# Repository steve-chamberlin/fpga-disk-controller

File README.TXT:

Compiled by Steve Chamberlin
steve@bigmessowires.com
January 28, 2019

//\\//\\//\\//\\//\\//\\//\\//\\//\\//\\//\\//\\//\\//\\//\\//\\//\\//\\//\\//\\

I'm sharing the FPGA disk controller design because I don't currently have the time or resources to pursue its further development on my own, but want the Apple II collector community to get the benefit of the progress I've made to date. 

See LICENSE.TXT for details on the license terms for this design.

The marks "Yellowstone", "BMOW", and "Big Mess o' Wires" are not covered by this license, and are reserved for my exclusive use. You are not permitted to use any of these words in the name of any clone or derivative products based on this design. You will need to choose a new name for your clone or derivative product.

//\\//\\//\\//\\//\\//\\//\\//\\//\\//\\//\\//\\//\\//\\//\\//\\//\\//\\//\\//\\

GROUND RULES
------------

Please don't send me detailed questions and requests for help with this design, or expect me to be your engineering consultant. I'm releasing the design to the community because I don't have time to pursue it myself. That means I can't work on it for you, either. The design is released as-is, with no promise of technical support. I may be able to answer general questions, but the rest is up to you.  

WHAT IS THIS?
-------------

Yellowstone is the code name for an Apple II disk controller card that's based on an FPGA, rather than using discrete logic chips and ROM chips. By reprogramming the FPGA, the card can be made to emulate various other disk controller cards made by Apple in the 1980s and 1990s. The work so far has focused on emulating an Apple Liron disk controller card, but it would also be easy to emulate a Disk II controller card. It's theoretically also possible to emulate a Disk 3.5 controller card, though this possibility has not been explored in detail.

WHAT'S LIRON?
-------------

The Liron disk controller was introduced by Apple in 1985. More formally known as the Apple II UniDisk 3.5 Controller, it's designed to work with a new generation of "smart" disk drives more sophisticated than the venerable Disk II 5.25 inch floppy drive. The smart disk port on the Liron is appropriately named the Smartport, and it can communicate with block-based storage devices such as the Unidisk 3.5 (an early 800K drive) and Smartport-based Apple II hard drives.

Why care about the Liron? The Apple IIc and Apple IIgs have integrated disk ports with built-in Smartport functionality, but for the earlier Apple II+ and IIe, the Liron is the only way to get a Smartport. For owners of the BMOW Floppy Emu disk emulator, having a Liron card makes it possible to use the Floppy Emu as an external hard drive for the II+ and IIe. Unfortunately finding a Liron is difficult, and although they occasionally turn up on eBay, they’re quite expensive. That makes cloning the Liron a desirable goal.

HOW IT WORKS
------------

The FPGA disk controller card is little more than an FPGA, a voltage regulator, and a set of level-shifting bus transceivers. The FPGA replaces all of the 7400-series discrete logic chips typically found on a disk controller card. Verilog (hardware description language) replacements for all of the 7400-series parts and other logic were written and programmed into the FPGA. This also includes a full Verilog implmentation of the Apple IWM chip. 

The FPGA also replaces the ROM chip containing the boot code for the card. The Apple II executes this code during power-up, and the code knows how to find and load sector 0 from the attached disk drive. The code was obtained from a ROM dump from a real Liron card.

The prototype card also includes a footprint for an 8-pin SPI flash memory chip. It is not used by the current FPGA code, and the chip can be omitted. The idea was that a small number of disk images could be stored in SPI flash memory, so the card could function both as a disk controller and as a disk emulator, but this was never implemented.

The card has a standard 10 x 2 pin disk connector on board. It can be connected directly to a BMOW Floppy Emu disk emulator, using a standard ribbon cable. But for a full Liron clone and connecton to a Unidisk 3.5, a DB-19 female connector is required. A design for a DB-19F adapter PCB is included here, and the adapter can be connected to the disk controller card with a short ribbon cable. The DB-19F is still available from surplus electronics suppliers in small quantities.

PROJECT STATUS
--------------

See https://www.bigmessowires.com/category/yellowstone/ for a complete history of work involving the FPGA disk controller.

The FPGA disk controller card was designed by Steve Chamberlin at Big Mess o' Wires during the summer of 2017, but the first prototype card wasn't built and tested until January 2018. The version 1.0 card had errors with the wiring for the output enable signal on one of the bus transceiver chips, and it required a few hand-soldered path wires to fix. After further development, the prototype card was demonstrated to work as a Liron clone, in both an Apple IIe enhanced computer and an Apple IIgs. It worked for controlling a real Unidisk 3.5 drive, as well as a BMOW Floppy Emu disk emulator configured for Smartport emulation mode.

Later testing discovered that the FPGA disk controller card worked reliably when it was the only card installed, but other cards were also present, it sometimes malfunctioned. The more other cards present, the worse the rate of errors became. This was diagnosed as a likely termination or contention problem on the Apple II data bus, and various fixes were tried unsuccessfully. After March 2018, I lost interest in researching the problem further, and no more work has occurred since then.

The design provided here is version 1.1, and it fixes the output enable problem from version 1.0.

WHERE TO START
--------------

Open the FPGA disk controller design (Liron clone) in EAGLE. Export Gerber files and send them to your favorite PCB fabricator. If desired, do the same for the DB19F adapter design.

Purchase the chips and other parts listed in the BOM. 

Assemble the card. I did it by hand, you can do it too. A syringe of solder paste and a hot plate or toaster oven works nicely.

Get a Lattice JTAG programmer or appropriate clone. Some clones don't handle 3.3V logic correctly. Maybe spend the extra money for a genuine Lattice programmer.

Install the Lattice Diamond software.

Apply 5V power to the card at jumper J4. Do not insert the card into your Apple II yet.

Program the FPGA with the bitstream for the Liron clone design - liron_fpgatop.jed

Insert the card in your Apple II. Remove any other cards that are present.

Connect a Smartport-compatible disk drive, such as a BMOW Floppy Emu disk emulator that's configured for Smartport emulation mode, or an Apple Unidisk 3.5 drive.

Turn on the Apple II. It should boot from the attached drive.

NEXT STEPS
----------

The bus termination or bus contention problem must be solved, in order to get a robust card that works smoothly when other cards are also present. See the blog posts from February-March 2018 for more details about what was already tried. A solution will require a person who's experienced at electronic design, and has appropriate test equipment such as an oscilloscope and logic analyzer.

The current design uses a Lattice MachXO2 1200HC FPGA, and a Lattice JTAG programmer (or compatible) is required for programming it. The XO2-1200HC has more logic resources than are actually necessary for the Liron clone design. The cheaper XO2-640 or XO2-256 could be substituted instead. They are mostly or entirely pin-compatible with the XO2-1200HC.

Programming the FPGA with a JTAG programmer is fine for development use, but end users are unlikely to have one. If reprogramming by the end user is desired (say to switch between Liron and Disk 3.5 emulation behaviors), a different method of FPGA programming will need to be developed.

FILES
-----

eagle/ - directory containing EAGLE designs for the FPGA disk controller card, the DB19F adapter, and a reverse-engineered schematic of the original Liron card.
eagle/FPGA disk controller/bom.xslx - bill of materials needed to assemble the card.
lattice/ - directory containing the Verilog and other code for the Liron clone design for the card.
yellowstone_blink/ - directory containing the Verilog and other code for a simple LED blink example. This can be used to verify that the FPGA is working.
yellowstone_blink_tcr.dir/ - directory containing some junk generated by the Lattice Diamond software.
disasm.asm, liron.asm - two different disassemblies of the original Liron card's boot ROM
LIRONALL.BIN - binary file with the original Liron card's boot ROM
rom-full-4k.mem - the Liron boot ROM in a format compatible with the Lattice Diamond software.
README.TXT - this file
LICENSE.TXT - details about the license for the design

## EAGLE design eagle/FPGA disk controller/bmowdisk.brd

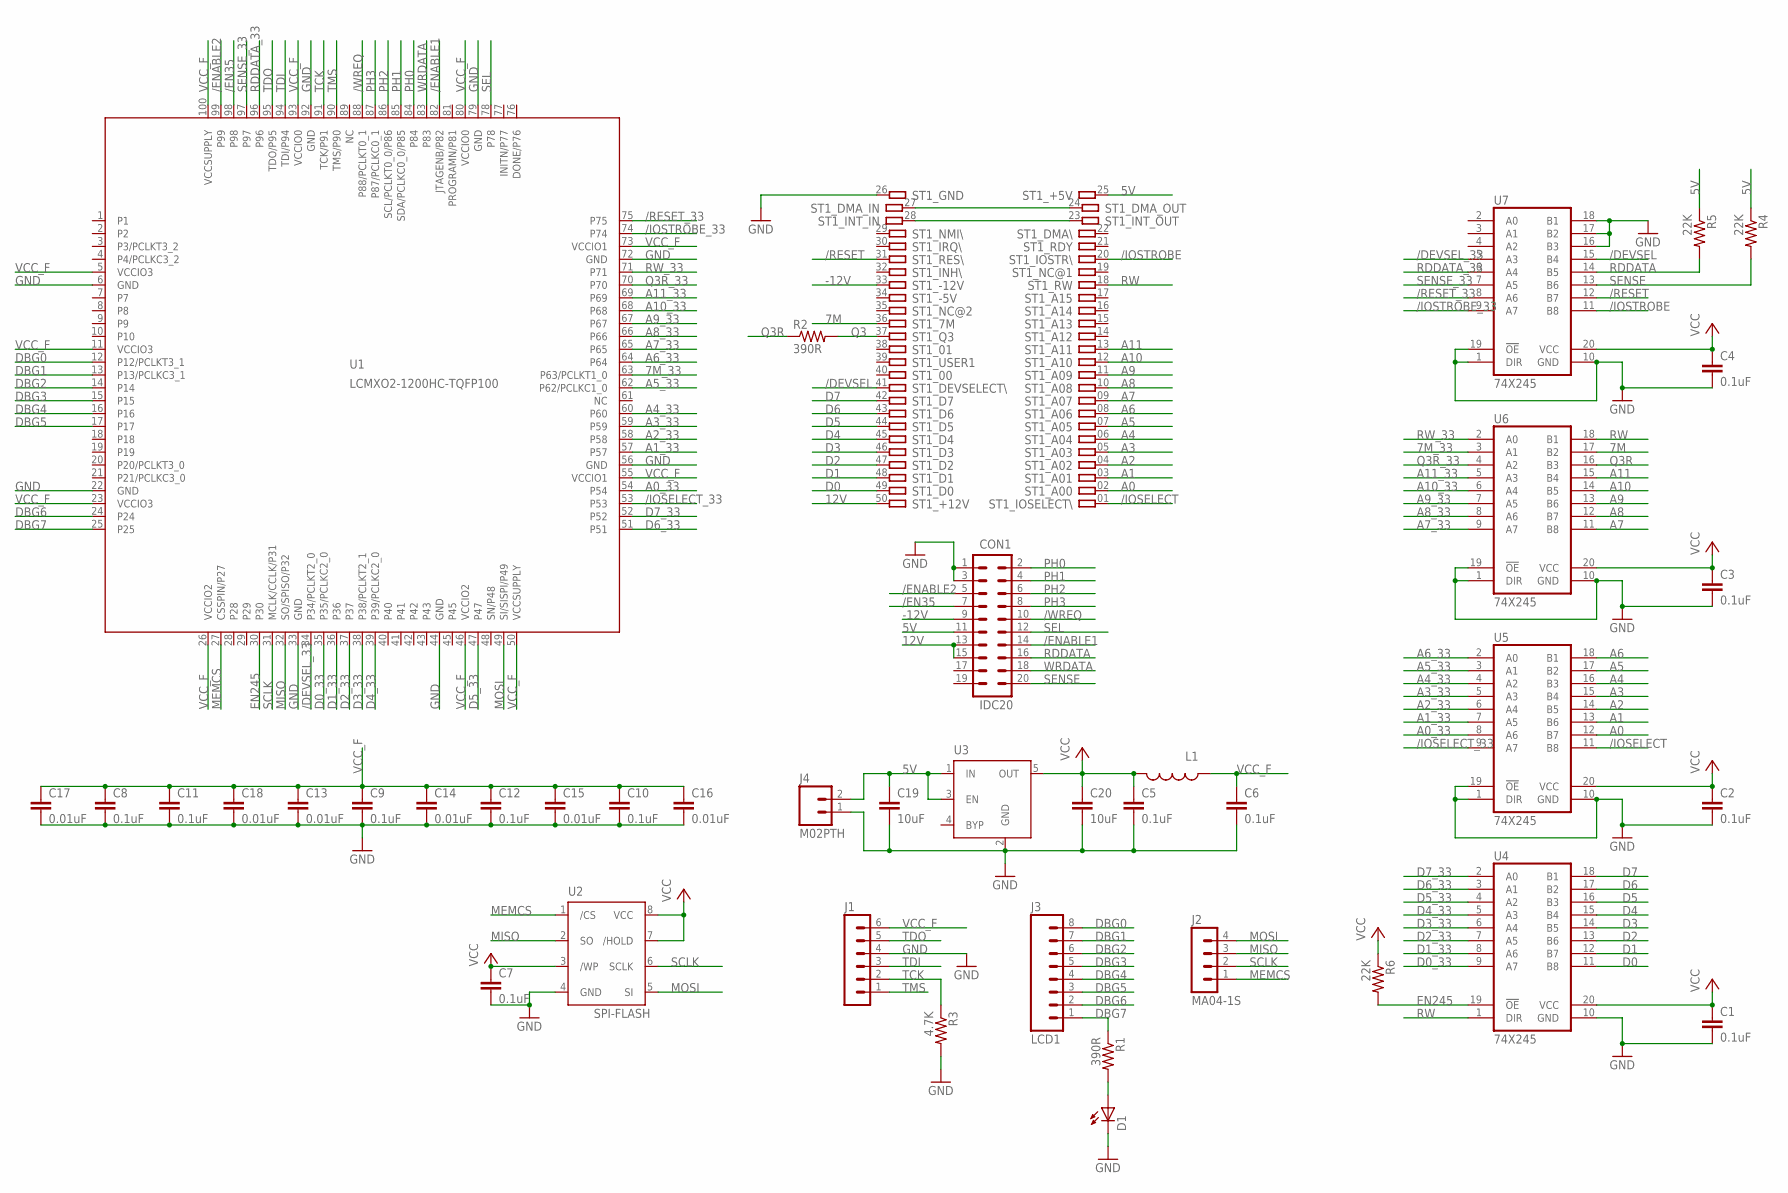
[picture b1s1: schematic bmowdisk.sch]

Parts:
C1, C2, C3, C4, C5, C6, C7, C8, C9, C10, C11, C12: 0.1uF; 0805
C13, C14, C15, C16, C17, C18: 0.01uF; 0805
C19, C20: 10uF; 0805
CON1: IDC20
D1: LEDCHIP-LED0805; CHIP-LED0805
J1: MA06-1NORMAL; MA06-1
J2: MA04-1S; MA04-1
J3: LCD1; 1X08
J4: M02PTH; 1X02
L1: INDUCTOR0805; 0805
R1, R2: 390R; 0805
R3: 4.7K; 0805
R4, R5, R6: 22K; 0805
ST1: A2-50PINMINI; A2-50PIN-MINI
U1: LCMXO2-1200HC-TQFP100; TQFP100
U2: SPI-FLASH; SOIC08
U3: MIC5219XX; SOT23-5
U4, U5, U6, U7: 74X245; SSOP20

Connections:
5V: C19.1, CON1.11, J4.2, R4.1, R5.1, ST1.25, U3.1 (IN), U3.3 (EN)
7M: ST1.36, U6.17 (B2)
7M_33: U1.63 (P63/PCLKT1_0), U6.3 (A1)
12V: CON1.13, CON1.15, ST1.50
-12V: CON1.9, ST1.33
/DEVSEL: ST1.41, U7.15 (B4)
/DEVSEL_33: U1.34 (P34/PCLKT2_0), U7.5 (A3)
/EN35: CON1.7, U1.98
/ENABLE1: CON1.14, U1.82 (JTAGENB/P82)
/ENABLE2: CON1.5, U1.99
/IOSELECT: ST1.01, U5.11 (B8)
/IOSELECT_33: U1.53, U5.9 (A7)
/IOSTROBE: ST1.20, U7.11 (B8)
/IOSTROBE_33: U1.74, U7.9 (A7)
/RESET: ST1.31, U7.12 (B7)
/RESET_33: U1.75, U7.8 (A6)
/WREQ: CON1.10, U1.88 (P88/PCLKT0_1)
A0: ST1.02, U5.12 (B7)
A0_33: U1.54, U5.8 (A6)
A1: ST1.03, U5.13 (B6)
A1_33: U1.57, U5.7 (A5)
A2: ST1.04, U5.14 (B5)
A2_33: U1.58, U5.6 (A4)
A3: ST1.05, U5.15 (B4)
A3_33: U1.59, U5.5 (A3)
A4: ST1.06, U5.16 (B3)
A4_33: U1.60, U5.4 (A2)
A5: ST1.07, U5.17 (B2)
A5_33: U1.62 (P62/PCLKC1_0), U5.3 (A1)
A6: ST1.08, U5.18 (B1)
A6_33: U1.64, U5.2 (A0)
A7: ST1.09, U6.11 (B8)
A7_33: U1.65, U6.9 (A7)
A8: ST1.10, U6.12 (B7)
A8_33: U1.66, U6.8 (A6)
A9: ST1.11, U6.13 (B6)
A9_33: U1.67, U6.7 (A5)
A10: ST1.12, U6.14 (B5)
A10_33: U1.68, U6.6 (A4)
A11: ST1.13, U6.15 (B4)
A11_33: U1.69, U6.5 (A3)
D0: ST1.49, U4.11 (B8)
D0_33: U1.35 (P35/PCLKC2_0), U4.9 (A7)
D1: ST1.48, U4.12 (B7)
D1_33: U1.36, U4.8 (A6)
D2: ST1.47, U4.13 (B6)
D2_33: U1.37, U4.7 (A5)
D3: ST1.46, U4.14 (B5)
D3_33: U1.38 (P38/PCLKT2_1), U4.6 (A4)
D4: ST1.45, U4.15 (B4)
D4_33: U1.39 (P39/PCLKC2_0), U4.5 (A3)
D5: ST1.44, U4.16 (B3)
D5_33: U1.47, U4.4 (A2)
D6: ST1.43, U4.17 (B2)
D6_33: U1.51, U4.3 (A1)
D7: ST1.42, U4.18 (B1)
D7_33: U1.52, U4.2 (A0)
DBG0: J3.8, U1.12 (P12/PCLKT3_1)
DBG1: J3.7, U1.13 (P13/PCLKC3_1)
DBG2: J3.6, U1.14
DBG3: J3.5, U1.15
DBG4: J3.4, U1.16
DBG5: J3.3, U1.17
DBG6: J3.2, U1.24
DBG7: J3.1, R1.1, U1.25
EN245: R6.2, U1.30, U4.19 (!OE)
GND: C1.2, C2.2, C3.2, C4.2, C5.2, C6.2, C7.2, C8.2, C9.2, C10.2, C11.2, C12.2, C13.2, C14.2, C15.2, C16.2, C17.2, C18.2, C19.2, C20.2, CON1.1, CON1.3, D1.C, J1.4, J4.1, R3.2, ST1.26, U1.6 (GND), U1.22 (GND), U1.33 (GND), U1.44 (GND), U1.56 (GND), U1.72 (GND), U1.79 (GND), U1.92 (GND), U2.4 (GND), U3.2 (GND), U4.10 (GND), U5.1 (DIR), U5.10 (GND), U5.19 (!OE), U6.1 (DIR), U6.10 (GND), U6.19 (!OE), U7.1 (DIR), U7.10 (GND), U7.16 (B3), U7.17 (B2), U7.18 (B1), U7.19 (!OE)
MEMCS: J2.1, U1.27 (CSSPIN/P27), U2.1 (/CS)
MISO: J2.3, U1.32 (SO/SPISO/P32), U2.2 (SO)
MOSI: J2.4, U1.49 (SI/SISPI/P49), U2.5 (SI)
unnamed: ST1.24, ST1.27
unnamed: ST1.23, ST1.28
unnamed: D1.A, R1.2
PH0: CON1.2, U1.84
PH1: CON1.4, U1.85 (SDA/PCLKC0_0/P85)
PH2: CON1.6, U1.86 (SCL/PCLKT0_0/P86)
PH3: CON1.8, U1.87 (P87/PCLKC0_1)
Q3: R2.2, ST1.37
Q3R: R2.1, U6.16 (B3)
Q3R_33: U1.70, U6.4 (A2)
RDDATA: CON1.16, R5.2, U7.14 (B5)
RDDATA_33: U1.96, U7.6 (A4)
RW: ST1.18, U4.1 (DIR), U6.18 (B1)
RW_33: U1.71, U6.2 (A0)
SCLK: J2.2, U1.31 (MCLK/CCLK/P31), U2.6 (SCLK)
SEL: CON1.12, U1.78
SENSE: CON1.20, R4.2, U7.13 (B6)
SENSE_33: U1.97, U7.7 (A5)
TCK: J1.2, R3.1, U1.91 (TCK/P91)
TDI: J1.3, U1.94 (TDI/P94)
TDO: J1.5, U1.95 (TDO/P95)
TMS: J1.1, U1.90 (TMS/P90)
VCC: C1.1, C2.1, C3.1, C4.1, C5.1, C7.1, C20.1, L1.2, R6.1, U2.3 (/WP), U2.7 (/HOLD), U2.8 (VCC), U3.5 (OUT), U4.20 (VCC), U5.20 (VCC), U6.20 (VCC), U7.20 (VCC)
VCC_F: C6.1, C8.1, C9.1, C10.1, C11.1, C12.1, C13.1, C14.1, C15.1, C16.1, C17.1, C18.1, J1.6, L1.1, U1.5 (VCCIO3), U1.11 (VCCIO3), U1.23 (VCCIO3), U1.26 (VCCIO2), U1.46 (VCCIO2), U1.50 (VCCSUPPLY), U1.55 (VCCIO1), U1.73 (VCCIO1), U1.80 (VCCIO0), U1.93 (VCCIO0), U1.100 (VCCSUPPLY)
WRDATA: CON1.18, U1.83

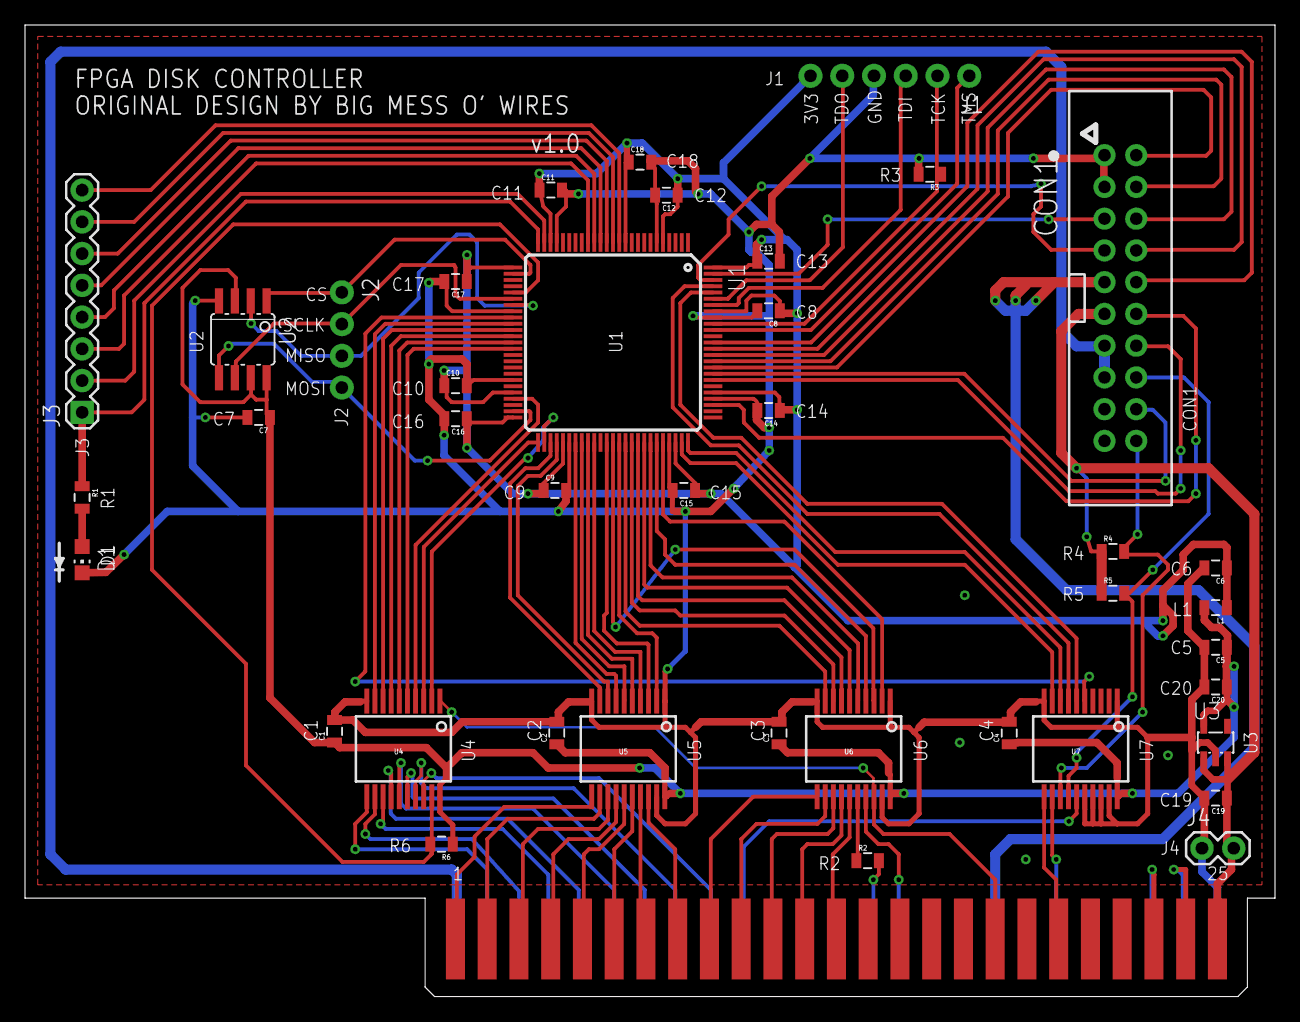
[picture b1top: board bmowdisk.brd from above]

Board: 2 copper layers, 100.0 x 77.7 mm, 41 parts (0 on the bottom side), 95 nets.

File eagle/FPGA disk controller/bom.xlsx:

Designation | Description | Manufacturer Part Number | Acceptable Substitutes | Source 1 | Source 2 | notes
U1 | MachXO2 1200HC FPGA, 100-pin TQFP package | Lattice LCMXO2-1200HC-4TG100C | none | https://www.digikey.com/product-detail/en/lattice-semiconduc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 |  | Could downsize to XO2-640 or XO2-256 if extra ROM space isn't needed. Confirm p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
U2 | SPI Flash memory, 8-pin SIOC package | Adesto AT25SF161-SSHD-T | similar | https://www.digikey.com/product-detail/en/adesto-technologie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 |  | Optional. Use for disk image storage, or ROM code if it's fast enough.
U3 | 300mA 3.3V LDO regulator, 5V input, SOT235 package | Micrel MIC5504-3.3YM5-TR | similar | https://www.digikey.com/product-detail/en/microchip-technolo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 | https://www.arrow.com/en/products/mic5504-3.3ym5-tr/microchi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
U4,U5,U6,U7 | 8-bit bus transceiver 74LVC245 | Nexperia 74LVC245ADB,118 | similar | https://www.digikey.com/product-detail/en/nexperia-usa-inc/7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,118/1727…
CON1 | IDC-20 male shrouded header | On Shore Technology 302-S201 | generic | http://www.digikey.com/product-detail/en/302-S201/ED10524-ND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 | http://www.digikey.com/product-detail/en/SBH11-PBPC-D10-ST-B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
J1 | 6x1 pin 0.1 inch male header, PTH | MC34743 | generic | http://www.newark.com/multicomp/mc34743/board-board-connecto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 | https://www.digikey.com/product-detail/en/sullins-connector-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 | Optional, JTAG port.
J2 | 4x1 pin 0.1 inch male header, PTH | MC34743 | generic | http://www.newark.com/multicomp/mc34743/board-board-connecto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 | https://www.digikey.com/product-detail/en/sullins-connector-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 | Optional, SPI port.
J3 | 8x1 pin 0.1 inch male header, PTH | MC34743 | generic | http://www.newark.com/multicomp/mc34743/board-board-connecto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 | https://www.digikey.com/product-detail/en/sullins-connector-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 | Optional, debug port.
J4 | 2x1 pin 0.1 inch male header, PTH | MC34743 | generic | http://www.newark.com/multicomp/mc34743/board-board-connecto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 | https://www.digikey.com/product-detail/en/sullins-connector-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 | Optional, 5V supply connector
D1 | LED, green, 0805 package, about 12 mcd | KP-2012SGC | generic | http://www.newark.com/kingbright/kp-2012sgc/led-green-1-25mm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 | https://www.digikey.com/product-detail/en/osram-opto-semicon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 | debug LED
L1 | ferrite bead 0805 | BKP2125HS600-T | generic | https://www.digikey.com/product-detail/en/taiyo-yuden/BKP212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
R1,R2 | 390 ohm resistor, 0805 package, 1/8W, 20% | RMCF0805JT390R | generic | https://www.digikey.com/product-detail/en/stackpole-electron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
R3 | 4.7K ohm resistor, 0805 package, 1/8W, 20% | RMCF0805JT4K70 | generic | https://www.digikey.com/product-detail/en/stackpole-electron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
R4,R5,R6 | 22K ohm resistor, 0805 package, 1/8W, 20% | RMCF0805JT22K0 | generic | https://www.digikey.com/product-detail/en/stackpole-electron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
C1-C12 | 0.1uF ceramic capacitor, 0805 package, 50V, 20% | CL21B104MBCNNNC | generic | https://www.digikey.com/product-detail/en/samsung-electro-me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
C13-C18 | 0.01uF ceramic capacitor, 0805 package, 50V, 20% | CL21B103KBANNNC | generic | https://www.digikey.com/product-detail/en/samsung-electro-me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
C19,C20 | 10uF ceramic capacitor, 0805 package, 6.3V, 20% | CL21A106KQCLRNC | generic | http://www.newark.com/avx/08056d106kat2a/ceramic-capacitor-1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 | https://www.digikey.com/product-detail/en/samsung-electro-me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
MISC1 | DB19-F |  |  |  |  | not required for Floppy Emu, but required for real drives
MISC2 | DB19-F adapter board |  |  |  |  | not required for Floppy Emu, but required for real drives

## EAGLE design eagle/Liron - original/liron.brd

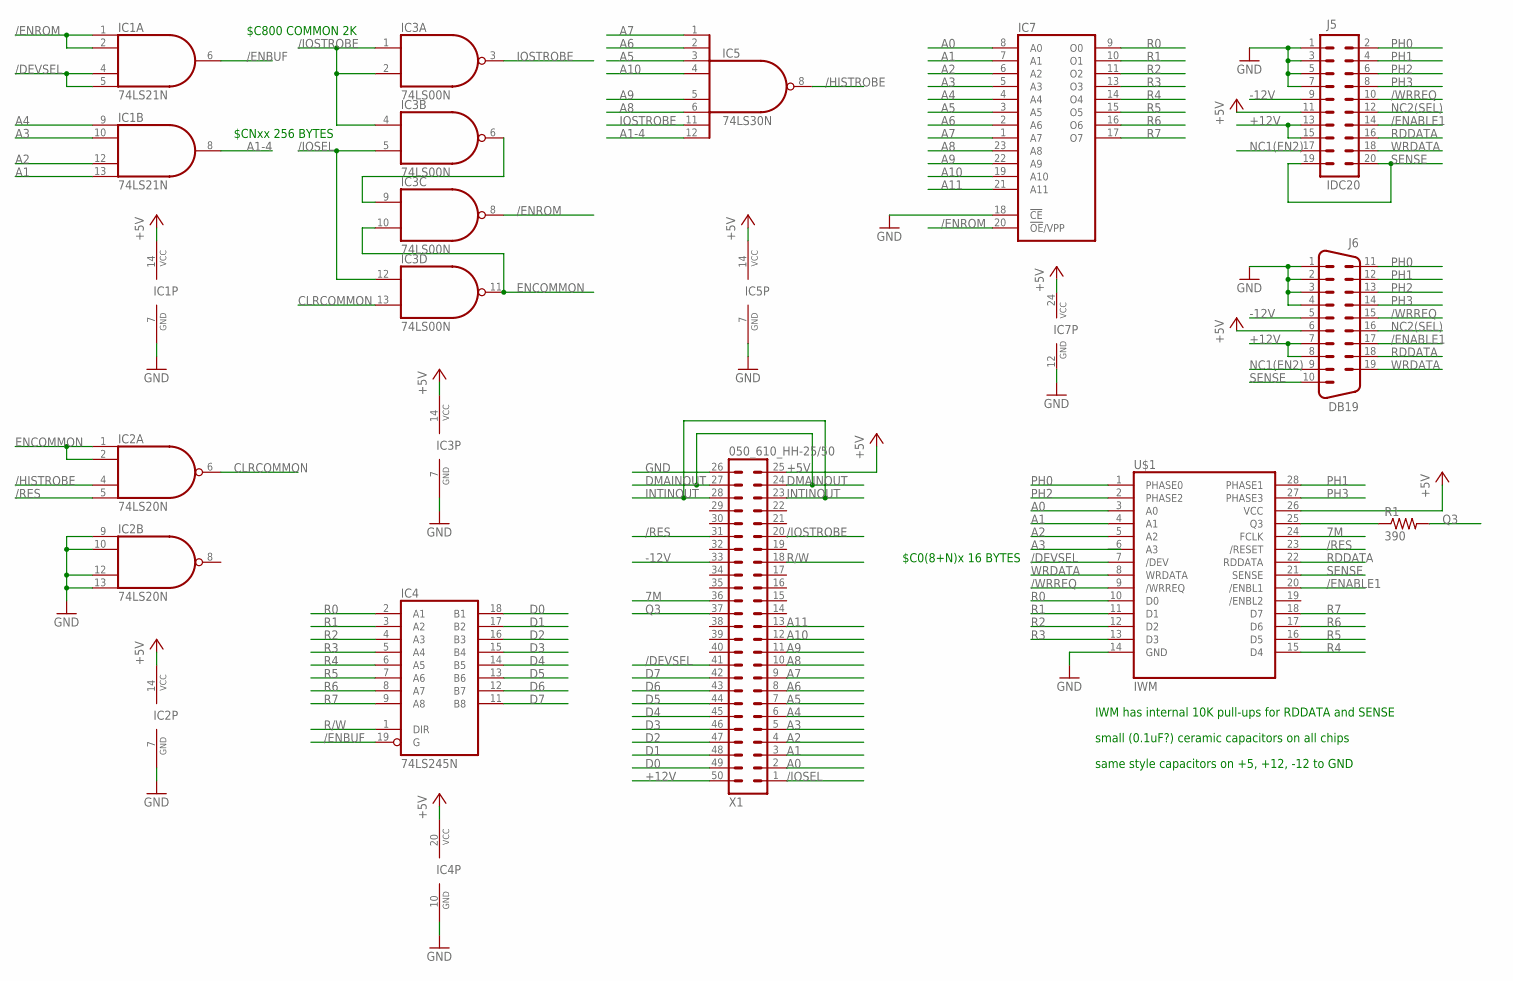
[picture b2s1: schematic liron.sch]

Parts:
IC1: 74LS21N; DIL14
IC2: 74LS20N; DIL14
IC3: 74LS00N; DIL14
IC4: 74LS245N; DIL20
IC5: 74LS30N; DIL14
IC7: 2732; DIL24
J5: IDC20
J6: DB19; DB19EDGE
R1: 390; 0805
U$1: IWM; DIL28
X1: 050_610_HH-25/50

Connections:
7M: U$1.24 (FCLK), X1.36 (40)
+5V: IC1.14 (VCC), IC2.14 (VCC), IC3.14 (VCC), IC4.20 (VCC), IC5.14 (VCC), IC7.24 (VCC), J5.11, J6.6, U$1.26 (VCC), X1.25
+12V: J5.13, J5.15, J6.7, J6.8, X1.50 (26)
-12V: J5.9, J6.5, X1.33 (43)
/DEVSEL: IC1.4 (I2), IC1.5 (I3), U$1.7 (/DEV), X1.41 (35)
/ENABLE1: J5.14, J6.17, U$1.20 (/ENBL1)
/ENBUF: IC1.6 (O), IC4.19 (G)
/ENROM: IC1.1 (I0), IC1.2 (I1), IC3.8 (O), IC7.20 (!OE!/VPP)
/HISTROBE: IC2.4 (I2), IC5.8 (O)
/IOSEL: IC3.5 (I1), IC3.12 (I0), X1.1
/IOSTROBE: IC3.1 (I0), IC3.2 (I1), IC3.4 (I0), X1.20
/RES: IC2.5 (I3), U$1.23 (/RESET), X1.31 (45)
/WRREQ: J5.10, J6.15, U$1.9 (/WRREQ)
A0: IC7.8 (A0), U$1.3 (A0), X1.2
A1: IC1.13 (I3), IC7.7 (A1), U$1.4 (A1), X1.3
A1-4: IC1.8 (O), IC5.12 (I7)
A2: IC1.12 (I2), IC7.6 (A2), U$1.5 (A2), X1.4
A3: IC1.10 (I1), IC7.5 (A3), X1.5
A4: IC1.9 (I0), IC7.4 (A4), X1.6
A5: IC5.3 (I2), IC7.3 (A5), X1.7
A6: IC5.2 (I1), IC7.2 (A6), X1.8
A7: IC5.1 (I0), IC7.1 (A7), X1.9
A8: IC5.6 (I5), IC7.23 (A8), X1.10
A9: IC5.5 (I4), IC7.22 (A9), X1.11
A10: IC5.4 (I3), IC7.19 (A10), X1.12
A11: IC7.21 (A11), X1.13
CLRCOMMON: IC2.6 (O), IC3.13 (I1)
D0: IC4.18 (B1), X1.49 (27)
D1: IC4.17 (B2), X1.48 (28)
D2: IC4.16 (B3), X1.47 (29)
D3: IC4.15 (B4), X1.46 (30)
D4: IC4.14 (B5), X1.45 (31)
D5: IC4.13 (B6), X1.44 (32)
D6: IC4.12 (B7), X1.43 (33)
D7: IC4.11 (B8), X1.42 (34)
DMAINOUT: X1.24, X1.27 (49)
ENCOMMON: IC2.1 (I0), IC2.2 (I1), IC3.10 (I1), IC3.11 (O)
GND: IC1.7 (GND), IC2.7 (GND), IC2.9 (I0), IC2.10 (I1), IC2.12 (I2), IC2.13 (I3), IC3.7 (GND), IC4.10 (GND), IC5.7 (GND), IC7.12 (GND), IC7.18 (!CE), J5.1, J5.3, J5.5, J5.7, J6.1, J6.2, J6.3, J6.4, U$1.14 (GND), X1.26 (50)
INTINOUT: X1.23, X1.28 (48)
IOSTROBE: IC3.3 (O), IC5.11 (I6)
unnamed: IC3.6 (O), IC3.9 (I0)
unnamed: R1.1, U$1.25 (Q3)
NC1(EN2): J5.17, J6.9
NC2(SEL): J5.12, J6.16
PH0: J5.2, J6.11, U$1.1 (PHASE0)
PH1: J5.4, J6.12, U$1.28 (PHASE1)
PH2: J5.6, J6.13, U$1.2 (PHASE2)
PH3: J5.8, J6.14, U$1.27 (PHASE3)
Q3: R1.2, X1.37 (39)
R0: IC4.2 (A1), IC7.9 (O0), U$1.10 (D0)
R1: IC4.3 (A2), IC7.10 (O1), U$1.11 (D1)
R2: IC4.4 (A3), IC7.11 (O2), U$1.12 (D2)
R3: IC4.5 (A4), IC7.13 (O3), U$1.13 (D3)
R4: IC4.6 (A5), IC7.14 (O4), U$1.15 (D4)
R5: IC4.7 (A6), IC7.15 (O5), U$1.16 (D5)
R6: IC4.8 (A7), IC7.16 (O6), U$1.17 (D6)
R7: IC4.9 (A8), IC7.17 (O7), U$1.18 (D7)
R/W: IC4.1 (DIR), X1.18
RDDATA: J5.16, J6.18, U$1.22 (RDDATA)
SENSE: J5.19, J5.20, J6.10, U$1.21 (SENSE)
WRDATA: J5.18, J6.19, U$1.8 (WRDATA)

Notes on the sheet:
$C800 COMMON 2K
$CNxx 256 BYTES
$C0(8+N)x 16 BYTES
small (0.1uF?) ceramic capacitors on all chips
same style capacitors on +5, +12, -12 to GND
IWM has internal 10K pull-ups for RDDATA and SENSE

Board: 2 copper layers, 11 parts (0 on the bottom side), 61 nets, no tracks yet.

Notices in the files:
parts and their libraries:
SparkFun-Connectors: Licensing: CC v3.0 Share-Alike You are welcome to use this library for commercial purposes.
